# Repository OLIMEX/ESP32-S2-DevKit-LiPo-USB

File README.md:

# ESP32-S2-DevKit-LiPo-USB
ESP32-S2 development board with native USB-OTG, the hardware supports both USB host and USB device functionality, LiPo battery charger and step up for handheld battery operation.

Product page: https://www.olimex.com/Products/IoT/ESP32-S2/ESP32-S2-DevKit-Lipo-USB/open-source-hardware
## License
* Hardware is released under CERN OHL v1.2 license
* Software is released under GPL3 License
* Documentation is released under CC BY-SA 3.0

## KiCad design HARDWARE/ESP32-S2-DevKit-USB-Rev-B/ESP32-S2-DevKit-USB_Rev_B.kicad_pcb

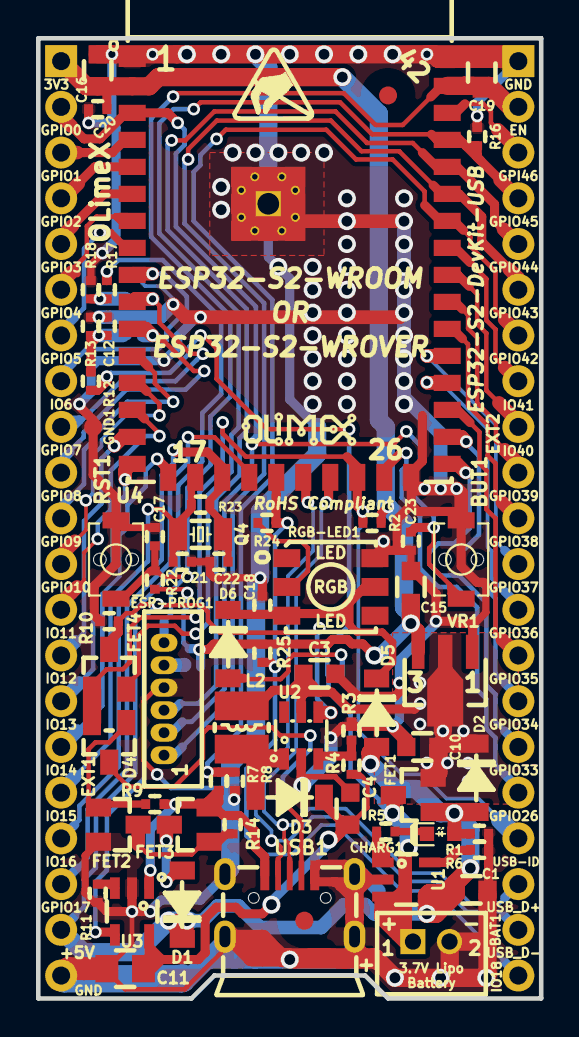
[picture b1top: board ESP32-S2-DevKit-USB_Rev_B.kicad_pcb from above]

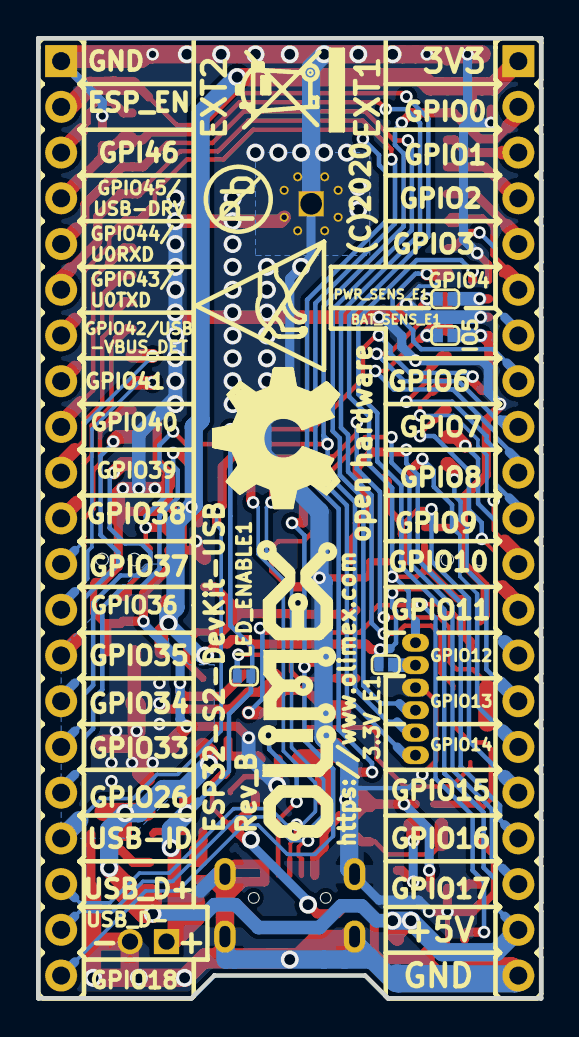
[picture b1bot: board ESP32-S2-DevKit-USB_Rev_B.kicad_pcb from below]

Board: 2 copper layers, 27.9 x 53.3 mm, 76 parts (11 on the bottom side), 62 nets.

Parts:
3.3V_E1: Opened; SJ_1_SMALLER
BAT1: DW02S; LIPO_BAT_VERTICAL_DW02S
BAT_SENS_E1: Opened; SJ_1_SMALLER
BUT1: IT-1185AU2-160G-G-TR; IT1185AU2_V2
C1: 10uF/6.3V/20%/X5R/C0603; C_0603_5MIL_DWS
C3, C4: 22uF/6.3V/C0603; C_0603_5MIL_DWS
C10, C15, C16: 22uF/6.3V/20%/X5R/C0603; C_0603_5MIL_DWS
C11: 47uF/6.3V/20%/X5R/C0805; C_0805_5MIL_DWS
C12, C18, C20: 100nF/10V/10%/X7R/C0402; C_0402_5MIL_DWS
C17, C23: NA(100nF/10V/10%/X7R/C0402); C_0402_5MIL_DWS
C19: 1uF/10V/10%/X5R/C0603; C_0603_5MIL_DWS
C21, C22: NA(22pF/50V/5%/COG/C0402); C_0402_5MIL_DWS
CHARG1: LED/YELLOW/0603; LED_0603_KA
D1, D2, D3, D6: 1N5819S4/SOD123; SOD-123_1C-2A_KA
D4: BAT54C(SOT23-3); SOT23-3
D5: 1N4148W/SOD123; SOD-123_1C-2A_KA
ESP-PROG1: WU06S
EXT1, EXT2: HN1x21
FET1, FET3, FET4: WPM2015-3/TR; SOT23
FET2: BSS138; SOT23
FID2, FID3: Fiducial; Fiducial1x3
GND1: TESTPAD; TESTPAD_40-ROUND
L2: 2.2uH/1.5A/DCR=72mR/20%/3.00x3.00x1.50mm/CD32(NR3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; CD32
LED_ENABLE1: Soldered; SJ_1_SMALLER
Logo_OSHW: LOGO_OPENHARDWARE_8x8
Olimex_Logo_Big: OLIMEX_LOGO_TB
Olimex_Logo_Small: LOGO_OLIMEX_80
PWR_SENS_E1: Opened; SJ_1_SMALLER
Q4: NA(Q32.768kHz/12.5pF/2P/SMD1206); CM7V-T1A(Crystal_Package-1206_3.20x1.50x0.65mm)
R1, R2, R9, R17, R22: 10k/R0402; R_0402_5MIL_DWS
R3: 130k/R0402; R_0402_5MIL_DWS
R4: 1M/R0402; R_0402_5MIL_DWS
R5, R6: 2.2k/R0402; R_0402_5MIL_DWS
R7, R10, R14, R16: 100k/R0402; R_0402_5MIL_DWS
R8: 220k/R0402; R_0402_5MIL_DWS
R11: 13k/1%/R0402; R_0402_5MIL_DWS
R12: 4.7M/R0402; R_0402_5MIL_DWS
R13, R25: 470k/R0402; R_0402_5MIL_DWS
R18: 1k/R0402; R_0402_5MIL_DWS
R23: NA(10M/R0402); R_0402_5MIL_DWS
R24: 22R/R0402; R_0402_5MIL_DWS
RGB-LED1: WS2812S(5X5MM); WS2812S(5x5MM)
RST1: IT-1185AU2-160G-G-TR; IT1185AU2_V2
Sign-Antistatic: LOGO_ANTISTATIC_1
Sign-Pb-Free: LOGO_PBFREE
Sign_Antistatic: Val**; LOGO_ANTISTATIC_SMALL_4.5mmX2.8mm
Sign_RecycleBin: LOGO_RECYCLEBIN_1
U1: BL4054B-42TPRN(SOT23-5); SOT-23-5
U2: MT3608(SOT23-6); SOT23-6
U3: SY6280AAC(SOT23-5); SOT-23-5
U4: ESP32-S2-WROVER_and_WROOM(PCB,-I(IPEX))-Universal; ESP32-S2-WROVER_MODULE
USB1: MISB-SWMM-5B-LF(USB_MICRO); USB-MICRO_MISB-SWMM-5B_LF
VR1: MCP1700T-3302E/MB; SOT89-3

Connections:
+3V3: 3.3V_E1.2, C15.1, C16.1, C20.2, EXT1.1, R2.2, R22.1, R25.1, U4.2, VR1.3
+5V: C1.1, CHARG1.2, D1.1, D2.2, D5.2, EXT1.20, FET1.1, R1.1, R17.1, U1.4
/5V_USB_HOST: C4.1, C11.1, D3.1, R4.1, U3.5
/+5V_USB: FET3.2, R7.2, R9.1, R14.1, U3.1, USB1.1
/ESP_EN\CHIP_PU: C17.2, C19.1, ESP-PROG1.6, EXT2.2, R22.2, RST1.1, U4.41
/GPI46: EXT2.3, U4.40
/GPIO0\BUT: BUT1.1, C23.2, ESP-PROG1.2, EXT1.2, U4.3
/GPIO1: EXT1.3, U4.4
/GPIO2: EXT1.4, U4.5
/GPIO3: EXT1.5, U4.6
/GPIO4: EXT1.6, U4.7
/GPIO5: EXT1.7, U4.8
/GPIO6: EXT1.8, U4.9
/GPIO7\PWR_SENS: EXT1.9, PWR_SENS_E1.2, U4.10
/GPIO8\BAT_SENS: BAT_SENS_E1.2, EXT1.10, U4.11
/GPIO9: EXT1.11, U4.12
/GPIO10: EXT1.12, U4.13
/GPIO11: EXT1.13, U4.14
/GPIO12: EXT1.14, U4.15
/GPIO13: EXT1.15, U4.16
/GPIO14: EXT1.16, U4.17
/GPIO15\XTAL_32K_P: C21.2, EXT1.17, Q4.1, R23.2, U4.18
/GPIO16\XTAL_32K_N: C22.2, EXT1.18, Q4.2, R23.1, U4.19
/GPIO17: EXT1.19, U4.20
/GPIO18\RGB_LED: EXT2.21, R24.1, R25.2, U4.21
/GPIO21\USB-ID: D4.2, EXT2.18, FET4.1, R2.1, U4.24
/GPIO26: EXT2.17, U4.25
/GPIO33: EXT2.16, U4.27
/GPIO34: EXT2.15, U4.28
/GPIO35: EXT2.14, U4.29
/GPIO36: EXT2.13, U4.30
/GPIO37: EXT2.12, U4.31
/GPIO38: EXT2.11, U4.32
/GPIO39: EXT2.10, U4.33
/GPIO40: EXT2.9, U4.34
/GPIO41: EXT2.8, U4.35
/GPIO42\USB-VBUS_DET: EXT2.7, R7.1, R8.2, U4.36
/GPIO43\U0TXD: ESP-PROG1.1, EXT2.6, U4.37
/GPIO44\U0RXD: ESP-PROG1.3, EXT2.5, U4.38
/GPIO45\USB-DRV: EXT2.4, FET4.2, R16.2, U4.39
/USB-DRV-E: FET4.3, R10.2, U2.4, U3.4
/USB-ID: D4.3, USB1.4
/USB_D+: EXT2.19, U4.23, USB1.3
/USB_D-: EXT2.20, U4.22, USB1.2
/Vin: C3.1, C10.1, D2.1, FET1.2, L2.1, U2.5, VR1.2
GND: BAT1.2, BUT1.2, C1.2, C3.2, C4.2, C10.2, C11.2, C12.1, C15.2, C16.2, C17.1, C18.1, C19.2, C20.1, C21.1, C22.1, C23.1, ESP-PROG1.4, EXT1.21, EXT2.1, FET2.2, GND1.1, R1.2, R3.1, R6.2, R8.1, R10.1, R11.1, R13.2, R16.1, R18.2, RGB-LED1.6, RST1.2, U1.2, U2.2, U3.2, U4.1, U4.26, U4.42, U4.43, USB1.0, USB1.5, VR1.1
unnamed: 3.3V_E1.1, ESP-PROG1.5
unnamed: BAT_SENS_E1.1, C12.2, R12.2, R13.1
unnamed: C18.2, D5.1, D6.1, RGB-LED1.3, RGB-LED1.5
unnamed: CHARG1.1, R5.1
unnamed: D1.2, FET3.3
unnamed: D3.2, L2.2, U2.1
unnamed: D4.1, FET2.1, R9.2
unnamed: D6.2, LED_ENABLE1.1
unnamed: FET2.3, FET3.1, R14.2
unnamed: PWR_SENS_E1.1, R17.2, R18.1
unnamed: R3.2, R4.2, U2.3
unnamed: R5.2, U1.1
unnamed: R6.1, U1.5
unnamed: R11.2, U3.3
unnamed: R24.2, RGB-LED1.2
VBAT: BAT1.1, FET1.3, LED_ENABLE1.2, R12.1, U1.3

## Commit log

2021-02-18 initial upload
2023-05-18 Update
    Updated instructions
2024-09-18 Update
    Added user's manual, removed outdated Arduino IDE guide
2026-03-10 Update
    Added new Arduino examples
2026-04-08 Update
    Added esphome and platformio configs

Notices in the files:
HARDWARE/ESP32-S2-DevKit-USB-Rev-B/ESP32-S2-DevKit-USB_Rev_B.kicad_pcb:
(C)2020
